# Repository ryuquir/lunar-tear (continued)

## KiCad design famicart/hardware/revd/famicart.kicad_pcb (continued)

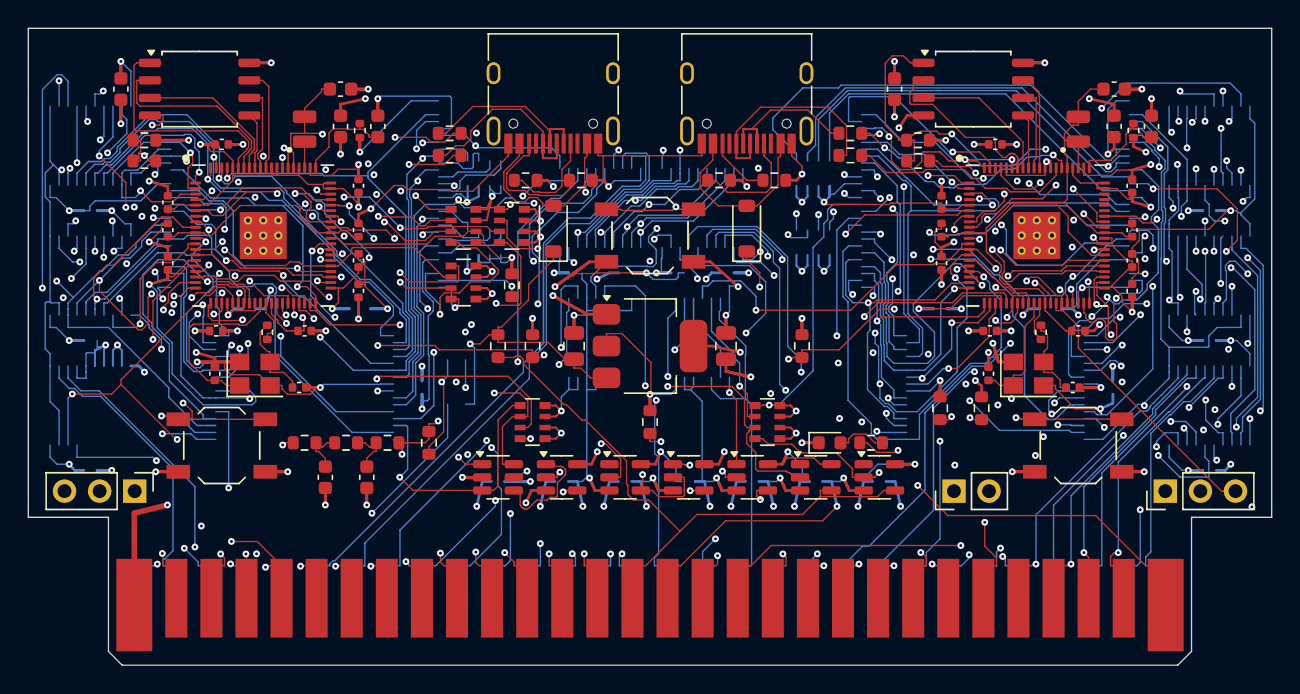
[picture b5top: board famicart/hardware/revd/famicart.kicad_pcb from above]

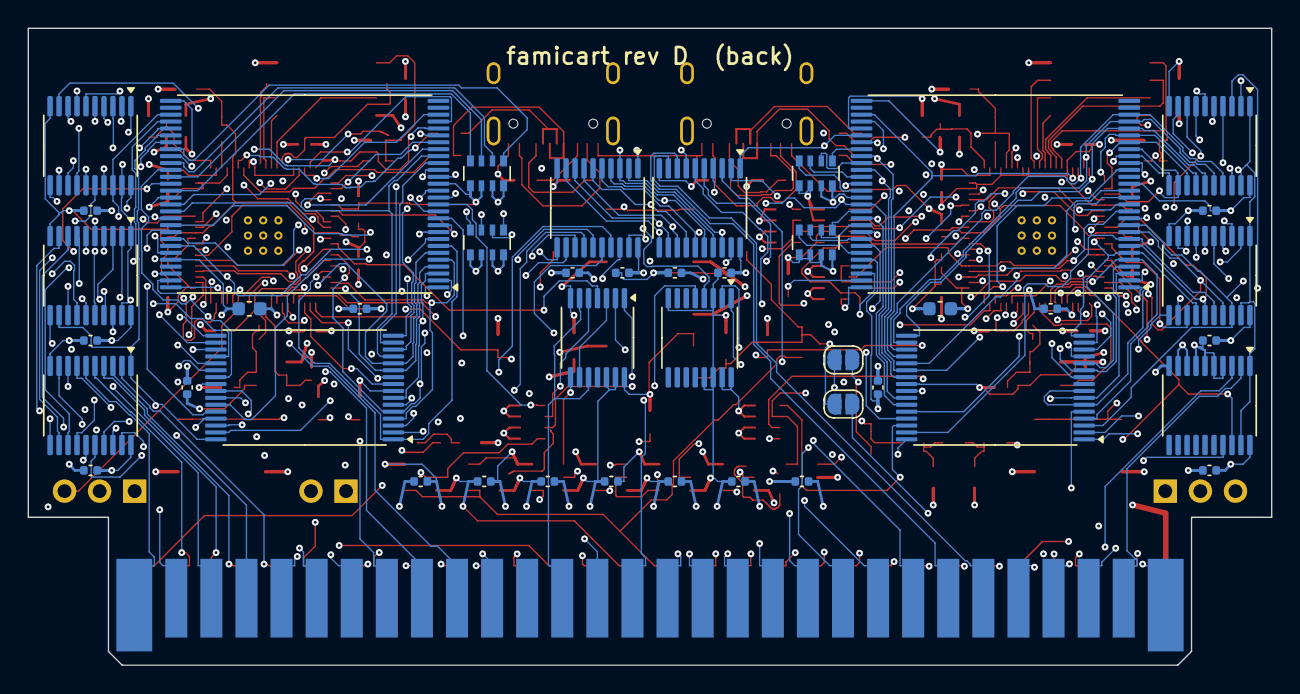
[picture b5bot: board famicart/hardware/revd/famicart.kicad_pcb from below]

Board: 6 copper layers, 90.0 x 46.1 mm, 140 parts (43 on the bottom side), 228 nets.

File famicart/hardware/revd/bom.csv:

Qty,Value,Footprint,References,Suggested part
1,Famicom 60-pin edge,Famicom_CardEdge_60,J1,"PCB card edge (gold fingers), no part"
2,RP2350B,QFN-80-1EP_10x10mm_P0.4mm_EP3.4x3.4mm,U1 U2,
2,W25Q16JVSSIQ,SOIC-8_5.23x5.23mm_P1.27mm,U3 U4,
2,100n,C_0603_1608Metric,C1 C17,X7R 0603 16V
9,10k,R_0603_1608Metric,R1 R7 R17 R22 R23 R24 R25 R26 R27,0603 1%
4,1k,R_0603_1608Metric,R2 R8 R21 R28,0603 1%
2,12MHz ABM8-272-T3,Crystal_SMD_3225-4Pin_3.2x2.5mm,Y1 Y2,
2,1k,R_0402_1005Metric,R3 R9,0603 1%
4,15p,C_0402_1005Metric,C2 C3 C18 C19,
2,3.3uH AOTA-B201610S3R3,L_0806_2016Metric,L1 L2,
6,4.7u,C_0603_1608Metric,C4 C5 C6 C20 C21 C22,
2,33,R_0402_1005Metric,R4 R10,
4,27,R_0603_1608Metric,R5 R6 R11 R12,
41,100n,C_0402_1005Metric,C7 C8 C9 C10 C11 C12 C13 C14 C15 C16 C23 C24 C25 C26 C27 C28 C29 C30 C31 C32 C37 C39 C41 C42 C43 C44 C45 C46 C47 C48 C49 C50 C51 C52 C53 C54 C55 C56 C57 C58 C59,X7R 0603 16V
1,USB-C PRG/mapper,USB_C_Receptacle_HRO_TYPE-C-31-M-12,J3,
4,5.1k,R_0603_1608Metric,R13 R14 R15 R16,0603 1% (USB-C CC pull-down)
1,USB-C CHR,USB_C_Receptacle_HRO_TYPE-C-31-M-12,J4,
2,B5819W,D_SOD-123,D1 D2,
1,RESET,SW_SPST_TL3342,SW1,E-Switch TL3342 / any 4.7x3.5 mm low-profile tactile
1,BOOTSEL A,SW_SPST_TL3342,SW2,
1,BOOTSEL B,SW_SPST_TL3342,SW3,
1,RUN/GND,PinHeader_1x02_P2.54mm_Vertical,J2,"2-pin 2.54 mm header (optional, wire to the console reset switch)"
1,SWD A,PinHeader_1x03_P2.54mm_Vertical,J5,
1,SWD B,PinHeader_1x03_P2.54mm_Vertical,J6,
1,AMS1117-3.3,SOT-223-3_TabPin2,U28,
2,10u,C_0805_2012Metric,C33 C34,X5R 0805 10V
2,2.2k,R_0603_1608Metric,R18 R19,0603 1%
1,4.7k,R_0603_1608Metric,R20,0603 1%
2,10n,C_0603_1608Metric,C35 C36,X7R 0603 50V
1,AUDIO bypass,SolderJumper-2_P1.3mm_Open_RoundedPad1.0x1.5mm,JP1,
1,CART_PRESENT,SolderJumper-2_P1.3mm_Open_RoundedPad1.0x1.5mm,JP2,
9,10k x4,R_Array_Convex_4x0603,RN1 RN2 RN3 RN4 RN5 RN6 RN7 RN8 RN9,
2,S29GL01GS 1Gbit NOR,TSOP-I-56_18.4x14mm_P0.5mm,U5 U6,
2,1u,C_0603_1608Metric,C38 C40,
1,FM28V100 128Kx8 F-RAM,TSOP-I-32_11.8x8mm_P0.5mm,U7,
1,IS62WV5128 512Kx8 SRAM,TSOP-I-32_11.8x8mm_P0.5mm,U8,
1,74LVC541 U9,TSSOP-20_4.4x6.5mm_P0.65mm,U9,
1,74LVC541 U10,TSSOP-20_4.4x6.5mm_P0.65mm,U10,
1,74LVC541 U11,TSSOP-20_4.4x6.5mm_P0.65mm,U11,
1,74LVC245 CPU data,TSSOP-20_4.4x6.5mm_P0.65mm,U12,
1,74LVC245 CPU->PPU data bridge,TSSOP-20_4.4x6.5mm_P0.65mm,U24,
1,74LVC139 CHR ROM/RAM select,TSSOP-16_4.4x5mm_P0.65mm,U22,
1,74LVC541 U17,TSSOP-20_4.4x6.5mm_P0.65mm,U17,
1,74LVC541 U18,TSSOP-20_4.4x6.5mm_P0.65mm,U18,
1,74LVC245 PPU data,TSSOP-20_4.4x6.5mm_P0.65mm,U19,
1,74LVC00 PPU access / CIRAM glue,TSSOP-14_4.4x5mm_P0.65mm,U20,
1,74LVC1G11 AND3: CPU data enable,SOT-23-6,U13,
1,74LVC1G32 OR: CPU 245 /OE,SOT-23-5,U14,
1,74LVC1G04 INV: R/W,SOT-23-5,U15,
1,74LVC1G00 NAND: WRAM /WE,SOT-23-5,U16,
1,74LVC1G32 OR: PPU 245 /OE,SOT-23-5,U21,
1,74LVC1G07 OD: /IRQ A,SOT-23-5,U26,
1,74LVC1G07 OD: /IRQ B,SOT-23-5,U27,
1,green 0603,LED_0603_1608Metric,D3,

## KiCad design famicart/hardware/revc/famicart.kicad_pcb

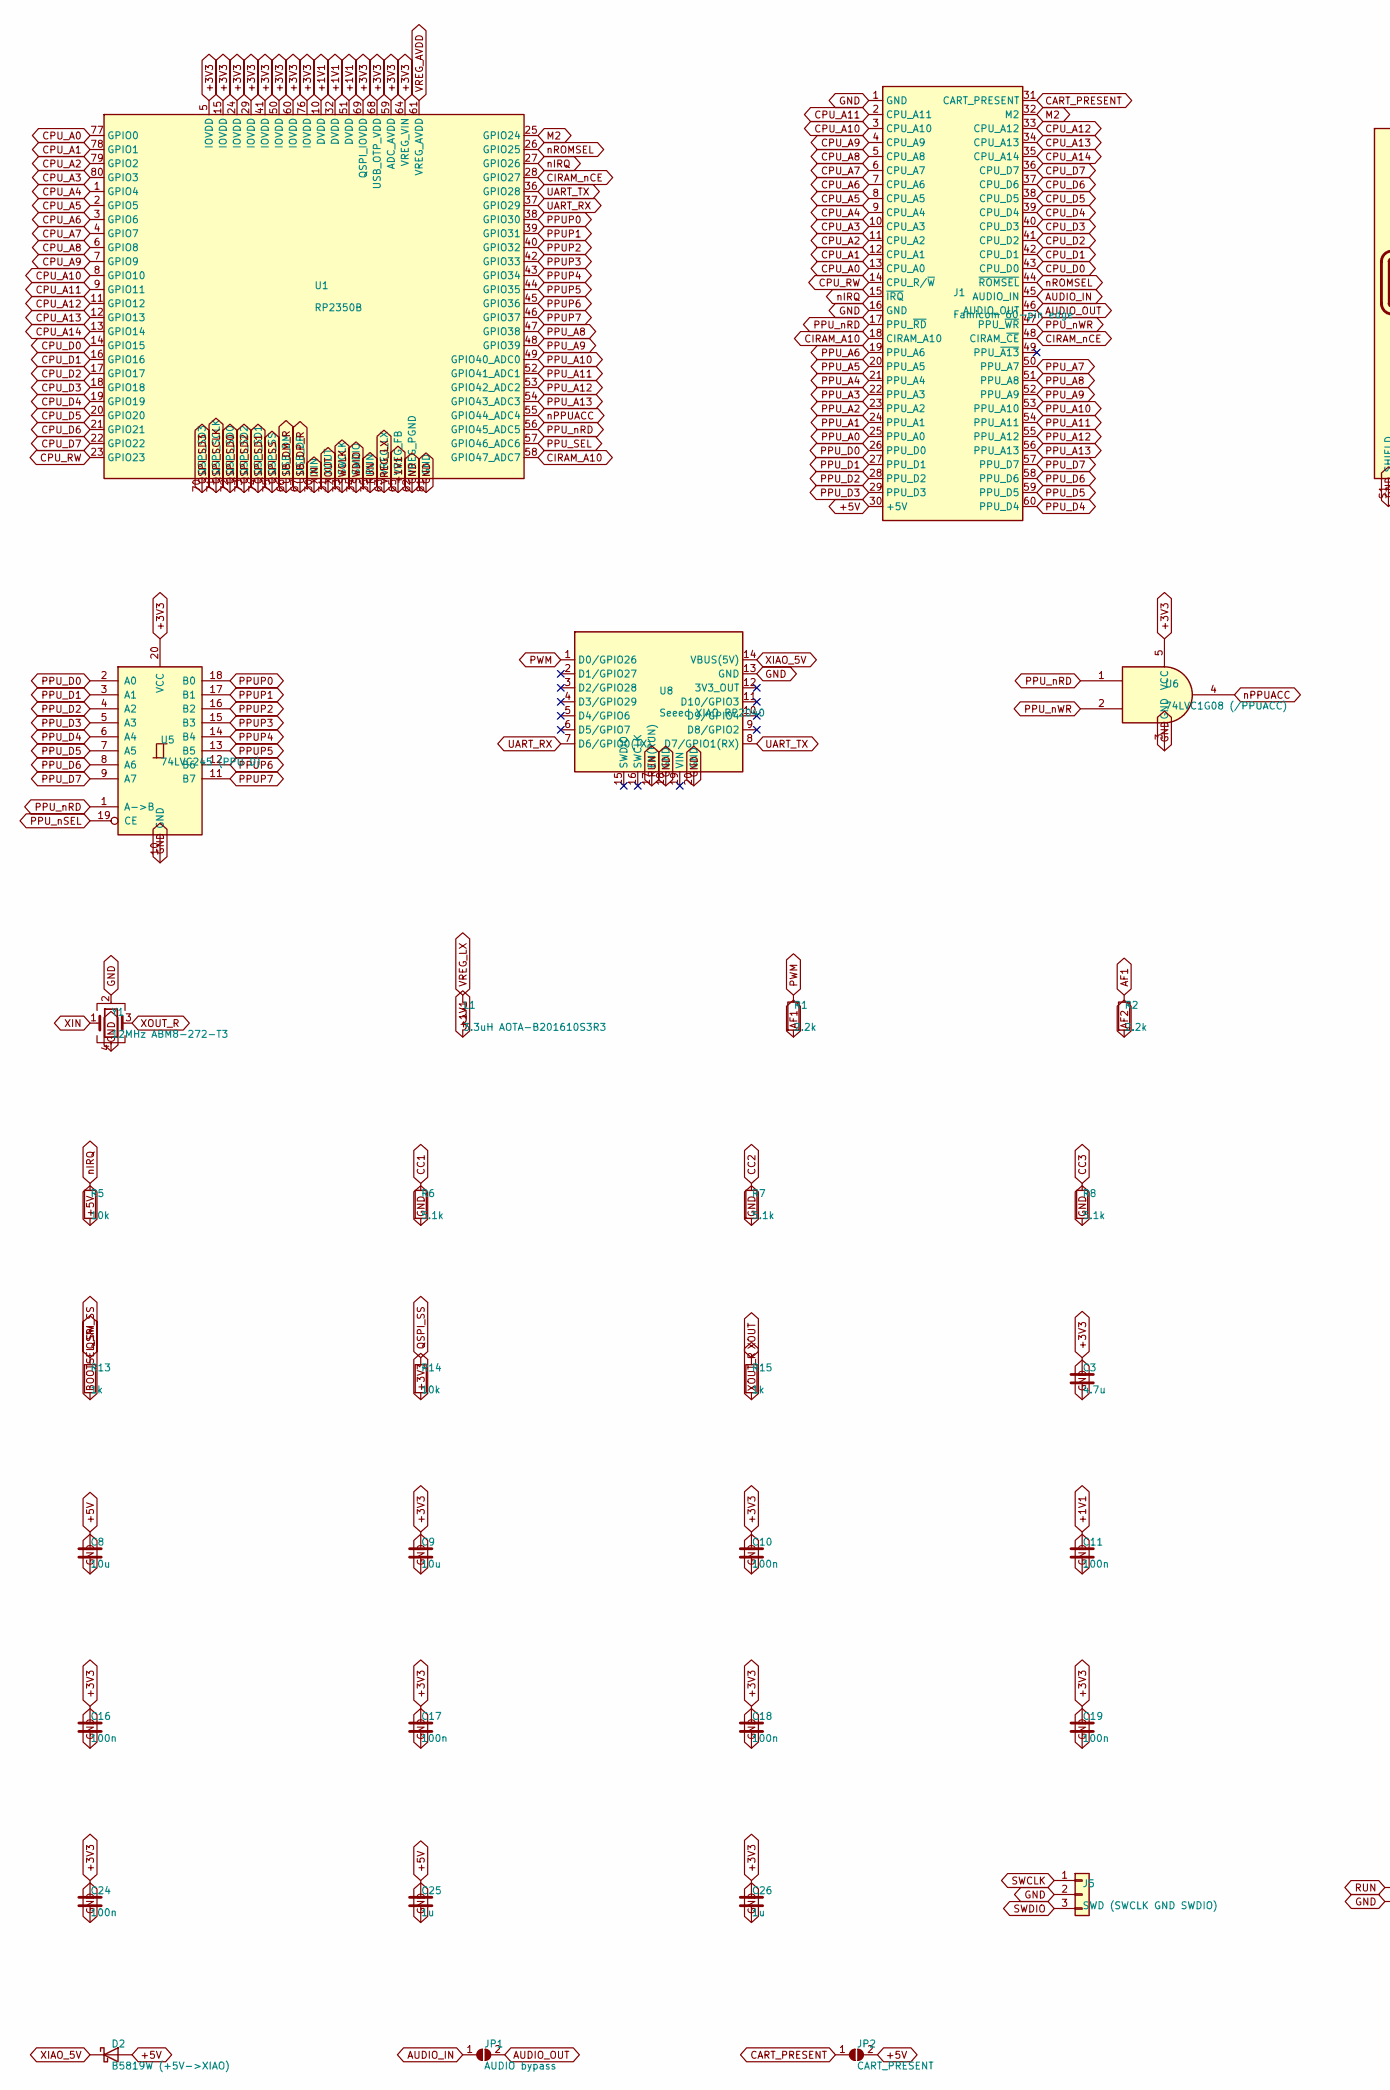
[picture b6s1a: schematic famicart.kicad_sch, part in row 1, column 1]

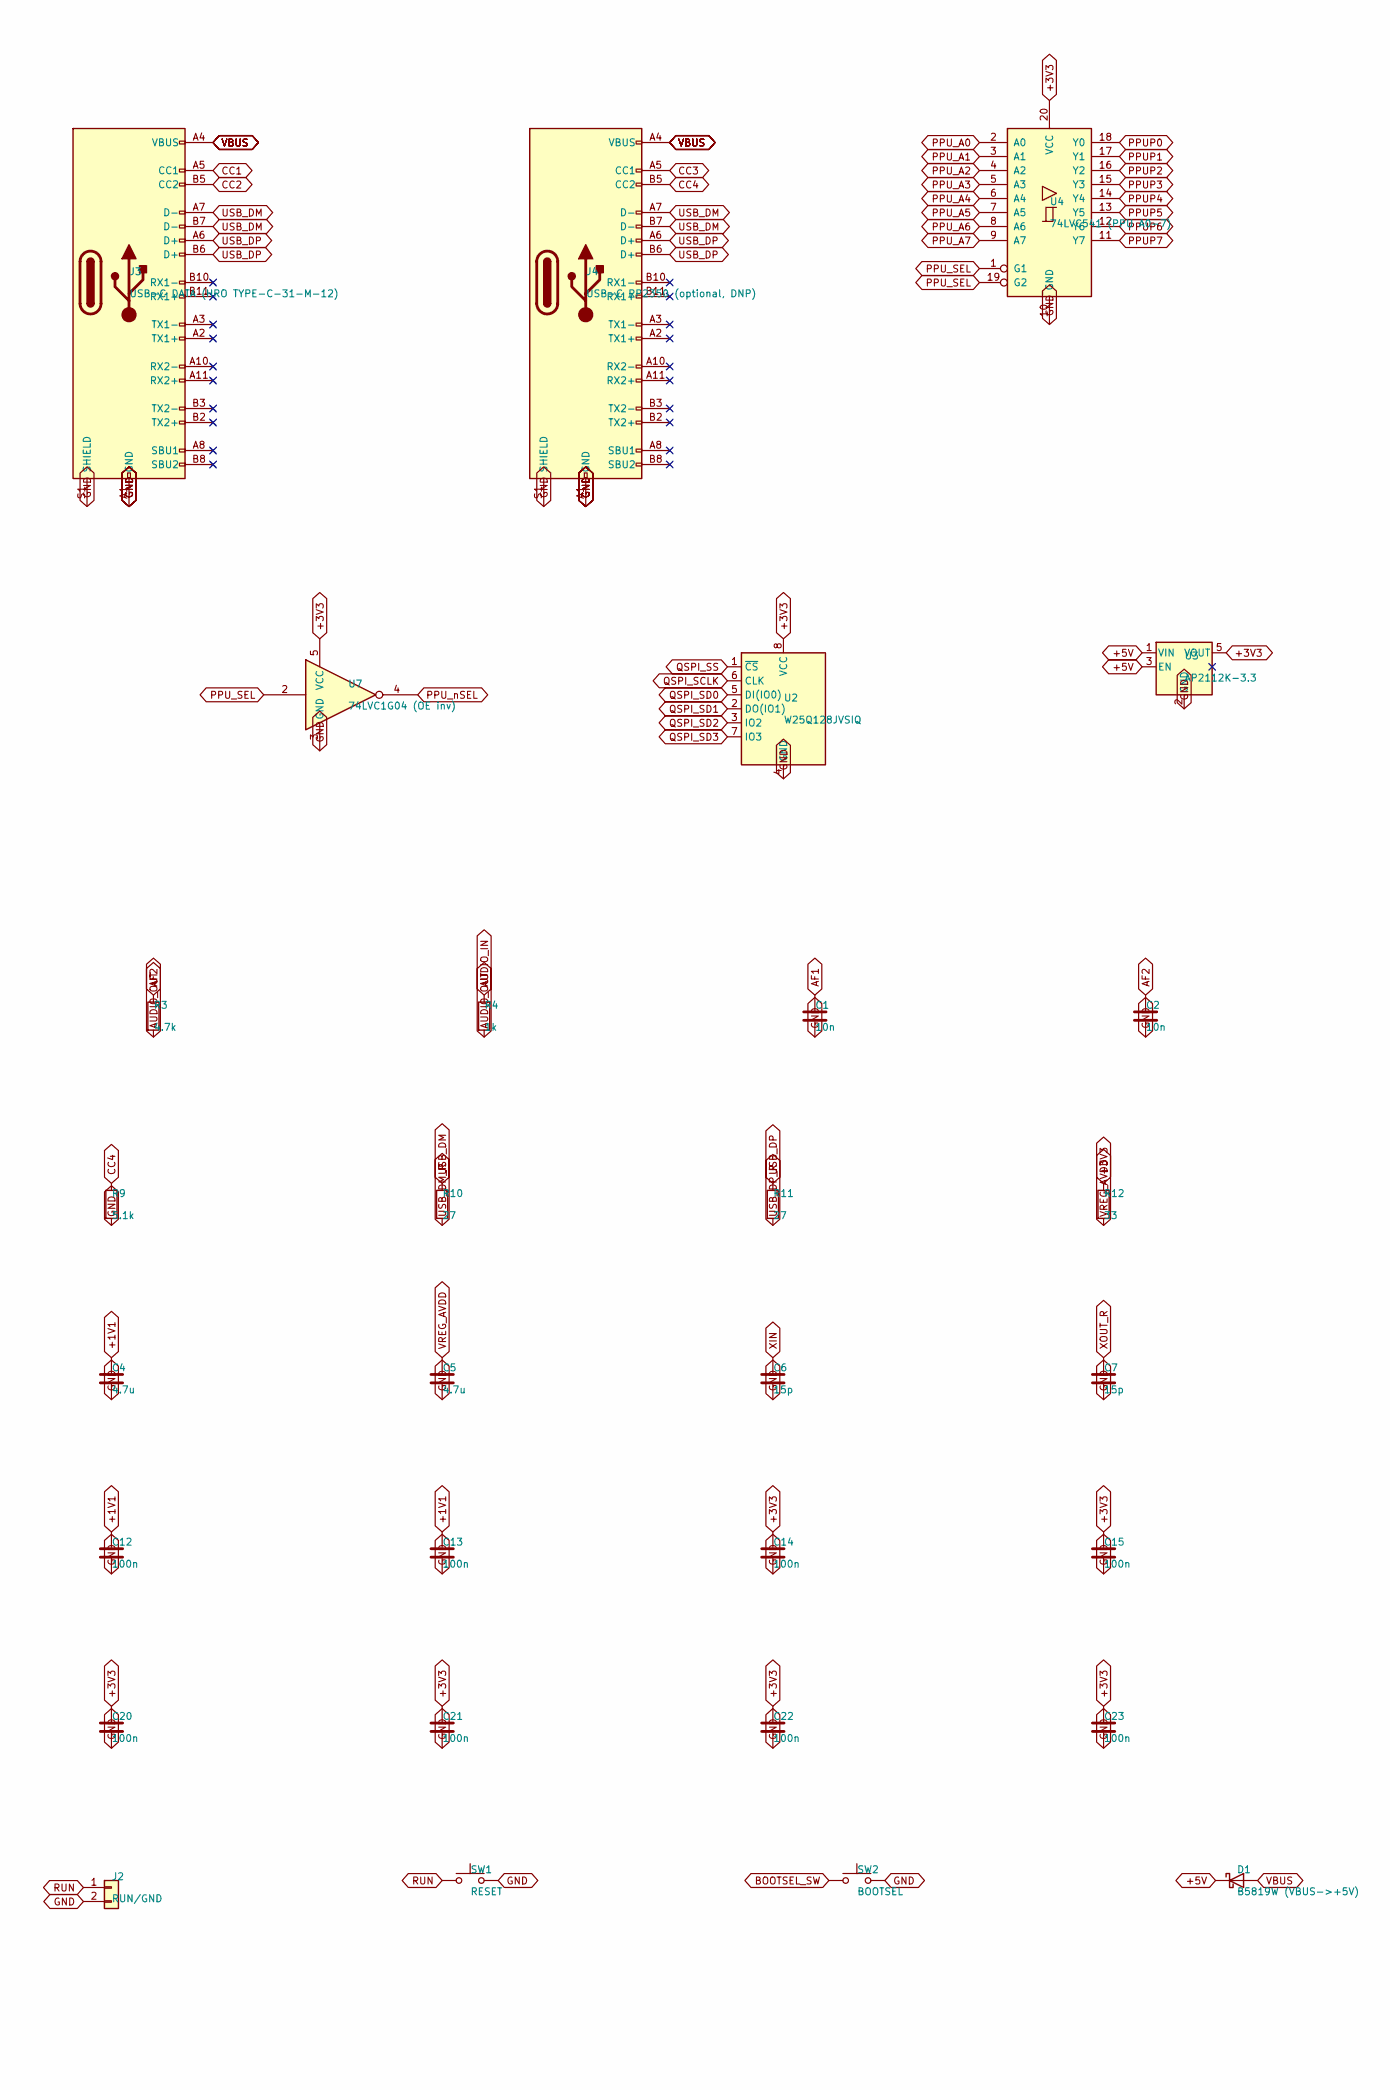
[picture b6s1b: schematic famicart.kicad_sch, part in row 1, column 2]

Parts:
C1, C2: 10n; C_0603_1608Metric
C3, C4, C5: 4.7u; C_0603_1608Metric
C6, C7: 15p; C_0402_1005Metric
C8, C9: 10u; C_0805_2012Metric
C10, C21, C22, C23, C24: 100n; C_0603_1608Metric
C11, C12, C13, C14, C15, C16, C17, C18, C19, C20: 100n; C_0402_1005Metric
C25, C26: 1u; C_0603_1608Metric
D1: B5819W (VBUS->+5V); D_SOD-123
D2: B5819W (+5V->XIAO); D_SOD-123
J1: Famicom 60-pin edge; Famicom_CardEdge_60
J2: RUN/GND; PinHeader_1x02_P2.54mm_Vertical
J3: USB-C DATA (HRO TYPE-C-31-M-12); USB_C_Receptacle_HRO_TYPE-C-31-M-12
J4: USB-C RP2350 (optional, DNP); USB_C_Receptacle_HRO_TYPE-C-31-M-12
J5: SWD (SWCLK GND SWDIO); PinHeader_1x03_P2.54mm_Vertical
JP1: AUDIO bypass; SolderJumper-2_P1.3mm_Open_RoundedPad1.0x1.5mm
JP2: CART_PRESENT; SolderJumper-2_P1.3mm_Open_RoundedPad1.0x1.5mm
L1: 3.3uH AOTA-B201610S3R3; L_0806_2016Metric
R1, R2: 2.2k; R_0603_1608Metric
R3: 4.7k; R_0603_1608Metric
R4, R13: 1k; R_0603_1608Metric
R5, R14: 10k; R_0603_1608Metric
R6, R7, R8, R9: 5.1k; R_0603_1608Metric
R10, R11: 27; R_0603_1608Metric
R12: 33; R_0402_1005Metric
R15: 1k; R_0402_1005Metric
SW1: RESET; SW_SPST_TL3342
SW2: BOOTSEL; SW_SPST_TL3342
U1: RP2350B; QFN-80-1EP_10x10mm_P0.4mm_EP3.4x3.4mm
U2: W25Q128JVSIQ; SOIC-8_5.23x5.23mm_P1.27mm
U3: AP2112K-3.3; SOT-23-5
U4: 74LVC541 (PPU A0-7); TSSOP-20_4.4x6.5mm_P0.65mm
U5: 74LVC245 (PPU D); TSSOP-20_4.4x6.5mm_P0.65mm
U6: 74LVC1G08 (/PPUACC); SOT-23-5
U7: 74LVC1G04 (OE inv); SOT-23-5
U8: Seeed XIAO RP2040; XIAO-RP2040-SMD
Y1: 12MHz ABM8-272-T3; Crystal_SMD_3225-4Pin_3.2x2.5mm

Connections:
+1V1: C4.1, C11.1, C12.1, C13.1, L1.2, U1.10 (DVDD), U1.32 (DVDD), U1.51 (DVDD), U1.65 (VREG_FB)
+3V3: C3.1, C9.1, C10.1, C14.1, C15.1, C16.1, C17.1, C18.1, C19.1, C20.1, C21.1, C22.1, C23.1, C24.1, C26.1, R12.1, R14.2, U1.5 (IOVDD), U1.15 (IOVDD), U1.24 (IOVDD), U1.29 (IOVDD), U1.41 (IOVDD), U1.50 (IOVDD), U1.59 (ADC_AVDD), U1.60 (IOVDD), U1.64 (VREG_VIN), U1.68 (USB_OTP_VDD), U1.69 (QSPI_IOVDD), U1.76 (IOVDD), U2.8 (VCC), U3.5 (VOUT), U4.20 (VCC), U5.20 (VCC), U6.5 (VCC), U7.5 (VCC)
+5V: C8.1, C25.1, D1.1 (K), D2.2 (A), J1.30 (+5V), JP2.2 (B), R5.2, U3.1 (VIN), U3.3 (EN)
AF1: C1.1, R1.2, R2.1
AF2: C2.1, R2.2, R3.1
AUDIO_IN: J1.45 (AUDIO_IN), JP1.1 (A), R4.1
AUDIO_OUT: J1.46 (AUDIO_OUT), JP1.2 (B), R3.2, R4.2
BOOTSEL_SW: R13.2, SW2.1
CART_PRESENT: J1.31 (CART_PRESENT), JP2.1 (A)
CC1: J3.A5 (CC1), R6.1
CC2: J3.B5 (CC2), R7.1
CC3: J4.A5 (CC1), R8.1
CC4: J4.B5 (CC2), R9.1
CIRAM_A10: J1.18 (CIRAM_A10), U1.58 (GPIO47_ADC7)
CIRAM_nCE: J1.48 (CIRAM_~CE), U1.28 (GPIO27)
CPU_A0: J1.13 (CPU_A0), U1.77 (GPIO0)
CPU_A1: J1.12 (CPU_A1), U1.78 (GPIO1)
CPU_A2: J1.11 (CPU_A2), U1.79 (GPIO2)
CPU_A3: J1.10 (CPU_A3), U1.80 (GPIO3)
CPU_A4: J1.9 (CPU_A4), U1.1 (GPIO4)
CPU_A5: J1.8 (CPU_A5), U1.2 (GPIO5)
CPU_A6: J1.7 (CPU_A6), U1.3 (GPIO6)
CPU_A7: J1.6 (CPU_A7), U1.4 (GPIO7)
CPU_A8: J1.5 (CPU_A8), U1.6 (GPIO8)
CPU_A9: J1.4 (CPU_A9), U1.7 (GPIO9)
CPU_A10: J1.3 (CPU_A10), U1.8 (GPIO10)
CPU_A11: J1.2 (CPU_A11), U1.9 (GPIO11)
CPU_A12: J1.33 (CPU_A12), U1.11 (GPIO12)
CPU_A13: J1.34 (CPU_A13), U1.12 (GPIO13)
CPU_A14: J1.35 (CPU_A14), U1.13 (GPIO14)
CPU_D0: J1.43 (CPU_D0), U1.14 (GPIO15)
CPU_D1: J1.42 (CPU_D1), U1.16 (GPIO16)
CPU_D2: J1.41 (CPU_D2), U1.17 (GPIO17)
CPU_D3: J1.40 (CPU_D3), U1.18 (GPIO18)
CPU_D4: J1.39 (CPU_D4), U1.19 (GPIO19)
CPU_D5: J1.38 (CPU_D5), U1.20 (GPIO20)
CPU_D6: J1.37 (CPU_D6), U1.21 (GPIO21)
CPU_D7: J1.36 (CPU_D7), U1.22 (GPIO22)
CPU_RW: J1.14 (CPU_R/~W), U1.23 (GPIO23)
GND: C1.2, C2.2, C3.2, C4.2, C5.2, C6.2, C7.2, C8.2, C9.2, C10.2, C11.2, C12.2, C13.2, C14.2, C15.2, C16.2, C17.2, C18.2, C19.2, C20.2, C21.2, C22.2, C23.2, C24.2, C25.2, C26.2, J1.1 (GND), J1.16 (GND), J2.2, J3.A1 (GND), J3.A12 (GND), J3.B1 (GND), J3.B12 (GND), J3.S1 (SHIELD), J4.A1 (GND), J4.A12 (GND), J4.B1 (GND), J4.B12 (GND), J4.S1 (SHIELD), J5.2, R6.2, R7.2, R8.2, R9.2, SW1.2, SW2.2, U1.62 (VREG_PGND), U1.81 (GND), U2.4 (GND), U3.2 (GND), U4.10 (GND), U5.10 (GND), U6.3 (GND), U7.3 (GND), U8.13 (GND), U8.18 (GND), U8.20 (GND), Y1.2, Y1.4
M2: J1.32 (M2), U1.25 (GPIO24)
PPUP0: U1.38 (GPIO30), U4.18 (Y0), U5.18 (B0)
PPUP1: U1.39 (GPIO31), U4.17 (Y1), U5.17 (B1)
PPUP2: U1.40 (GPIO32), U4.16 (Y2), U5.16 (B2)
PPUP3: U1.42 (GPIO33), U4.15 (Y3), U5.15 (B3)
PPUP4: U1.43 (GPIO34), U4.14 (Y4), U5.14 (B4)
PPUP5: U1.44 (GPIO35), U4.13 (Y5), U5.13 (B5)
PPUP6: U1.45 (GPIO36), U4.12 (Y6), U5.12 (B6)
PPUP7: U1.46 (GPIO37), U4.11 (Y7), U5.11 (B7)
PPU_A0: J1.25 (PPU_A0), U4.2 (A0)
PPU_A1: J1.24 (PPU_A1), U4.3 (A1)
PPU_A2: J1.23 (PPU_A2), U4.4 (A2)
PPU_A3: J1.22 (PPU_A3), U4.5 (A3)
PPU_A4: J1.21 (PPU_A4), U4.6 (A4)
PPU_A5: J1.20 (PPU_A5), U4.7 (A5)
PPU_A6: J1.19 (PPU_A6), U4.8 (A6)
PPU_A7: J1.50 (PPU_A7), U4.9 (A7)
PPU_A8: J1.51 (PPU_A8), U1.47 (GPIO38)
PPU_A9: J1.52 (PPU_A9), U1.48 (GPIO39)
PPU_A10: J1.53 (PPU_A10), U1.49 (GPIO40_ADC0)
PPU_A11: J1.54 (PPU_A11), U1.52 (GPIO41_ADC1)
PPU_A12: J1.55 (PPU_A12), U1.53 (GPIO42_ADC2)
PPU_A13: J1.56 (PPU_A13), U1.54 (GPIO43_ADC3)
PPU_D0: J1.26 (PPU_D0), U5.2 (A0)
PPU_D1: J1.27 (PPU_D1), U5.3 (A1)
PPU_D2: J1.28 (PPU_D2), U5.4 (A2)
PPU_D3: J1.29 (PPU_D3), U5.5 (A3)
PPU_D4: J1.60 (PPU_D4), U5.6 (A4)
PPU_D5: J1.59 (PPU_D5), U5.7 (A5)
PPU_D6: J1.58 (PPU_D6), U5.8 (A6)
PPU_D7: J1.57 (PPU_D7), U5.9 (A7)
PPU_SEL: U1.57 (GPIO46_ADC6), U4.1 (G1), U4.19 (G2), U7.2
PPU_nRD: J1.17 (PPU_~RD), U1.56 (GPIO45_ADC5), U5.1 (A->B), U6.1
PPU_nSEL: U5.19 (CE), U7.4
PPU_nWR: J1.47 (PPU_~WR), U6.2
PWM: R1.1, U8.1 (D0/GPIO26)
QSPI_SCLK: U1.71 (QSPI_SCLK), U2.6 (CLK)
QSPI_SD0: U1.72 (QSPI_SD0), U2.5 (DI(IO0))
QSPI_SD1: U1.74 (QSPI_SD1), U2.2 (DO(IO1))
QSPI_SD2: U1.73 (QSPI_SD2), U2.3 (IO2)
QSPI_SD3: U1.70 (QSPI_SD3), U2.7 (IO3)
QSPI_SS: R13.1, R14.1, U1.75 (QSPI_SS), U2.1 (~CS)
RUN: J2.1, SW1.1, U1.35 (RUN), U8.17 (EN(RUN))
SWCLK: J5.1, U1.33 (SWCLK)
SWDIO: J5.3, U1.34 (SWDIO)
UART_RX: U1.37 (GPIO29), U8.7 (D6/GPIO0(TX))
UART_TX: U1.36 (GPIO28), U8.8 (D7/GPIO1(RX))
USB_DM: J3.A7 (D-), J3.B7 (D-), J4.A7 (D-), J4.B7 (D-), R10.1
USB_DM_R: R10.2, U1.66 (USB_DM)
USB_DP: J3.A6 (D+), J3.B6 (D+), J4.A6 (D+), J4.B6 (D+), R11.1
USB_DP_R: R11.2, U1.67 (USB_DP)
VBUS: D1.2 (A), J3.A4 (VBUS), J3.A9 (VBUS), J3.B4 (VBUS), J3.B9 (VBUS), J4.A4 (VBUS), J4.A9 (VBUS), J4.B4 (VBUS), J4.B9 (VBUS)
VREG_AVDD: C5.1, R12.2, U1.61 (VREG_AVDD)
VREG_LX: L1.1, U1.63 (VREG_LX)
XIAO_5V: D2.1 (K), U8.14 (VBUS(5V))
XIN: C6.1, U1.30 (XIN), Y1.1
XOUT: R15.1, U1.31 (XOUT)
XOUT_R: C7.1, R15.2, Y1.3
nIRQ: J1.15 (~IRQ), R5.1, U1.27 (GPIO26)
nPPUACC: U1.55 (GPIO44_ADC4), U6.4
nROMSEL: J1.44 (~ROMSEL), U1.26 (GPIO25)

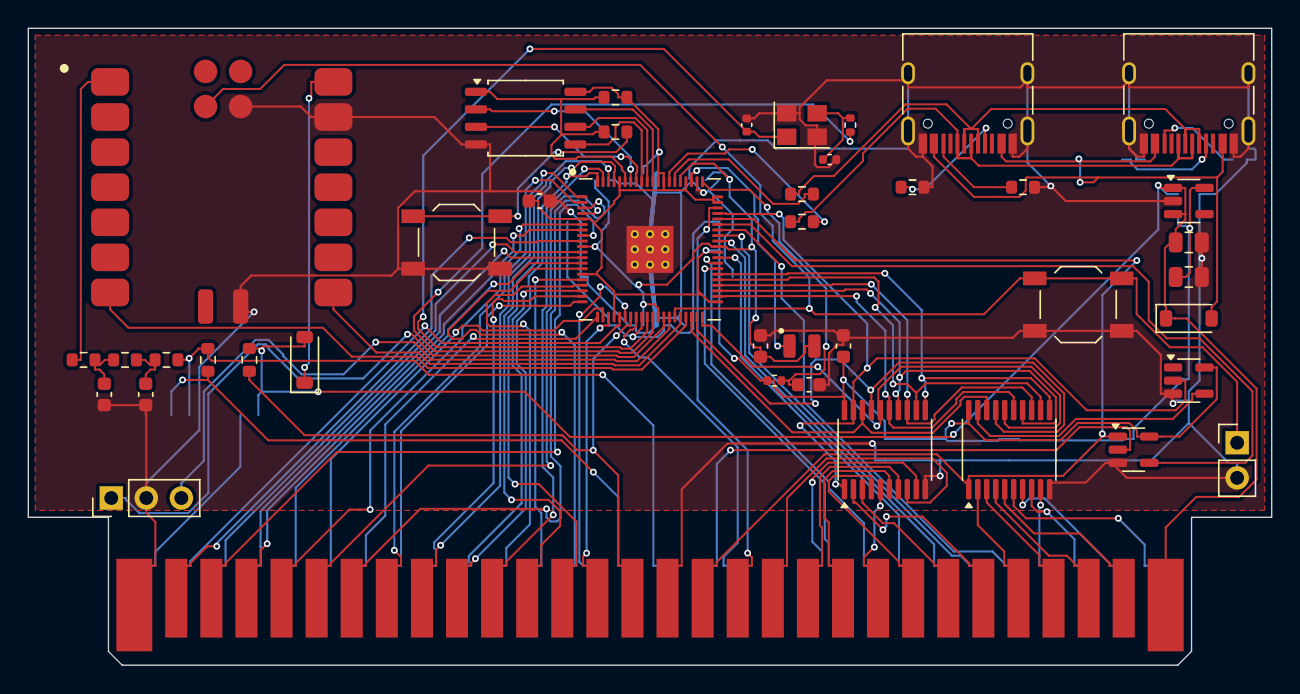
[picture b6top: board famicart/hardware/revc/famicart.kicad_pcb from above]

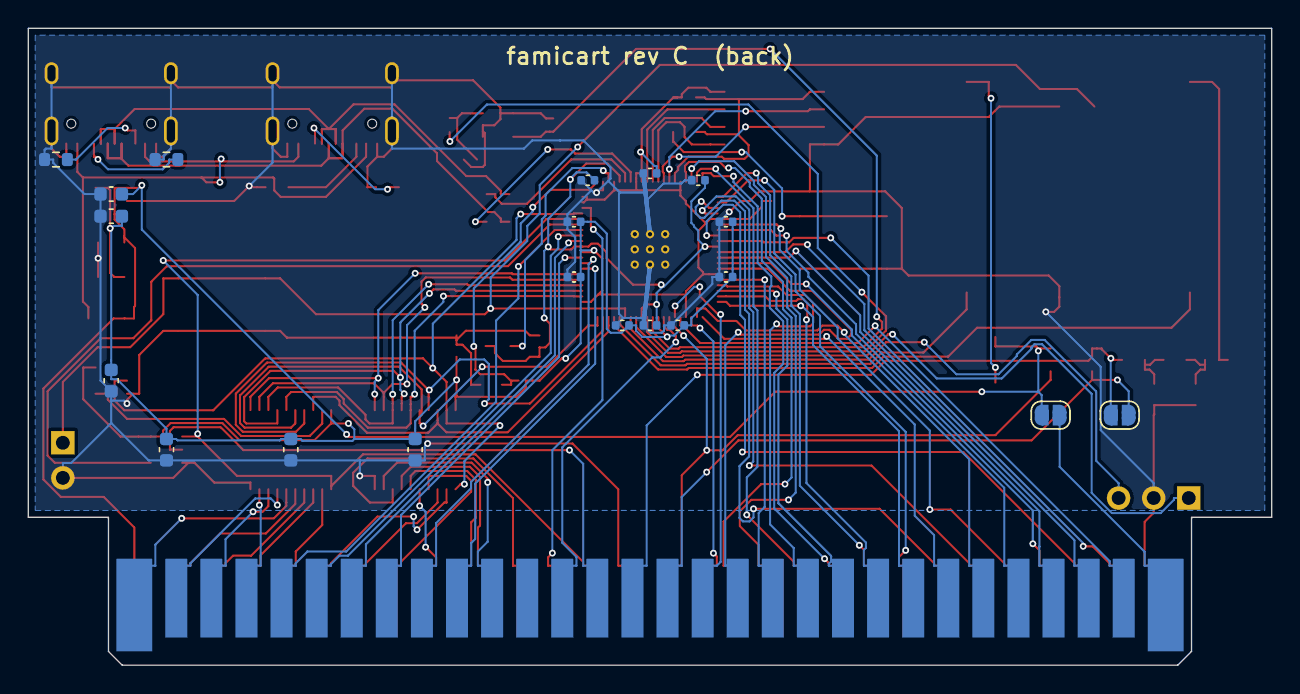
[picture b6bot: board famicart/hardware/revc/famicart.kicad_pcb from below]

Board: 2 copper layers, 90.0 x 46.1 mm, 62 parts (20 on the bottom side), 101 nets.

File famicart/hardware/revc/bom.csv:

Qty,Value,Footprint,References,Suggested part
1,Famicom 60-pin edge,Famicom_CardEdge_60,J1,"PCB card edge (gold fingers), no part"
1,RP2350B,QFN-80-1EP_10x10mm_P0.4mm_EP3.4x3.4mm,U1,
1,W25Q128JVSIQ,SOIC-8_5.23x5.23mm_P1.27mm,U2,
1,AP2112K-3.3,SOT-23-5,U3,
1,74LVC541,TSSOP-20_4.4x6.5mm_P0.65mm,U4,Nexperia 74LVC541APW (TSSOP-20)
1,74LVC245,TSSOP-20_4.4x6.5mm_P0.65mm,U5,Nexperia 74LVC245APW (TSSOP-20)
1,74LVC1G08,SOT-23-5,U6,Nexperia 74LVC1G08GW / TI SN74LVC1G08DBV
1,74LVC1G04,SOT-23-5,U7,
1,Seeed XIAO RP2040,XIAO-RP2040-SMD,U8,
1,12MHz ABM8-272-T3,Crystal_SMD_3225-4Pin_3.2x2.5mm,Y1,
1,3.3uH AOTA-B201610S3R3,L_0806_2016Metric,L1,
1,USB-C DATA,USB_C_Receptacle_HRO_TYPE-C-31-M-12,J3,
1,USB-C RP2350,USB_C_Receptacle_HRO_TYPE-C-31-M-12,J4,
1,RUN/GND,PinHeader_1x02_P2.54mm_Vertical,J2,"2-pin 2.54 mm header (optional, wire to the console reset switch)"
1,SWD,PinHeader_1x03_P2.54mm_Vertical,J5,
1,RESET,SW_SPST_TL3342,SW1,E-Switch TL3342 / any 4.7x3.5 mm low-profile tactile
1,BOOTSEL,SW_SPST_TL3342,SW2,
2,2.2k,R_0603_1608Metric,R1 R2,0603 1%
1,4.7k,R_0603_1608Metric,R3,0603 1%
2,1k,R_0603_1608Metric,R4 R13,0603 1%
2,10n,C_0603_1608Metric,C1 C2,X7R 0603 50V
2,10k,R_0603_1608Metric,R5 R14,0603 1%
4,5.1k,R_0603_1608Metric,R6 R7 R8 R9,0603 1% (USB-C CC pull-down)
2,27,R_0603_1608Metric,R10 R11,
1,33,R_0402_1005Metric,R12,
1,1k,R_0402_1005Metric,R15,0603 1%
3,4.7u,C_0603_1608Metric,C3 C4 C5,
2,15p,C_0402_1005Metric,C6 C7,
2,10u,C_0805_2012Metric,C8 C9,X5R 0805 10V
5,100n,C_0603_1608Metric,C10 C21 C22 C23 C24,X7R 0603 16V
2,B5819W,D_SOD-123,D1 D2,
1,AUDIO bypass,SolderJumper-2_P1.3mm_Open_RoundedPad1.0x1.5mm,JP1,
1,CART_PRESENT,SolderJumper-2_P1.3mm_Open_RoundedPad1.0x1.5mm,JP2,
10,100n,C_0402_1005Metric,C11 C12 C13 C14 C15 C16 C17 C18 C19 C20,X7R 0603 16V
2,1u,C_0603_1608Metric,C25 C26,

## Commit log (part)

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2026-03-16 [major, quest flow fix]
2026-03-17 Refactor Gacha and Scene Management in README and Code
    - Updated README to reflect changes in bootstrap options, replacing `--bootstrap-profile` with `--scene` for user initialization.
    - Refactored main.go to accommodate the new scene-based bootstrapping, enhancing user state management.
    - Adjusted Gacha catalog loading and related functions to ensure consistency with updated identifiers and improve clarity in asset resolution.
    - Removed obsolete functions and variables related to Gacha and quest handling, streamlining the codebase for better maintainability.
2026-03-18 Remove mock package and enhance quest flow engine with new scene and costume management
    - Deleted the mock package as it was no longer needed.
    - Introduced new types for scene grants and costumes in the quest flow engine to improve data handling.
    - Updated the engine to apply scene grants during quest progress, enhancing user experience.
    - Modified user state to include weapon notes and ensure comprehensive updates across user interactions.
2026-03-19 Update .gitignore and remove empty .keep file in frida directory
    - Added 'frida/' to .gitignore to exclude the frida directory from version control.
    - Deleted the empty .keep file in the frida directory to clean up the project structure.
2026-03-19 Refactor Quest Handling and Improve Logging
    - Updated ApplyBootstrap method to replace panic with a fatal log for unknown scene IDs, enhancing error handling.
    - Modified HandleQuestFinish method to include an isRetired parameter, improving quest completion logic.
    - Added new user data types (IUserConsumableItem, IUserMaterial, IUserImportantItem) to various service components for better state management.
    - Cleaned up state projection by removing unused user data types, streamlining data representation.
2026-03-20 Add Tutorial Unlock Conditions and Update User State Management
    - Introduced tutorialUnlockCondition struct to manage tutorial unlock criteria, enhancing tutorial progression logic.
    - Updated Engine to load tutorial unlock conditions from JSON, improving initialization of tutorial states.
    - Refactored UserState to use a map for storing multiple tutorial progress states, allowing for better management of user tutorials.
    - Enhanced state projection to sort and represent tutorial progress accurately, ensuring comprehensive user data handling.
2026-03-22 Enhance Quest Flow with Battle Drop Rewards
    - Updated the quest engine to include battle drop rewards, allowing for dynamic reward allocation based on quest completion.
    - Modified the StartMainQuest and FinishMainQuest methods to return battle drop rewards in the response, improving user feedback during quest progression.
    - Introduced new data structures for managing battle drop rewards and pickup reward groups, enhancing the overall quest reward system.
2026-03-22 Refactor Server into Domain-Oriented Architecture
    - Extract repository interfaces (UserRepository, SessionRepository,
    GachaRepository) from monolithic store.go; move MemoryStore to
    store/memory/ sub-package with error returns for DB compatibility
    - Split questflow/engine.go (1451 lines) into engine, rewards, battle,
    bootstrap, scene files
    - Replace monolithic state_projection.go with table-driven projector
2026-03-24 Enhance Main Quest Scene Progress Handling
    - Added logic to determine if the user has reached the last quest scene, updating MainQuest.IsReachedLastQuestScene accordingly.
    - Updated user portal cage status to reflect current progress and latest version during scene progress handling.
    - Adjusted user data diff to include IUserPortalCageStatus and IUserQuest, improving state management during quest updates.
2026-03-25 Add Snapshot Management for User State
    - Introduced snapshot functionality to save and load user state based on the current quest scene.
    - Updated MemoryStore to handle snapshot directory and scene ID during user state updates.
    - Enhanced user state initialization to load from snapshots if available, improving user experience during quest progression.
    - Added new methods for saving and loading snapshots in memory store, ensuring persistent user state across sessions.
    - Updated .gitignore to exclude snapshot files from version control.
2026-03-25 Implement Character Viewer Feature
    - Added CharacterViewer service to manage character viewing functionality.
    - Introduced CharacterViewerCatalog to handle character viewer fields and their release conditions.
    - Updated gRPC server to register the new CharacterViewer service and its dependencies.
    - Modified Makefile to include the new proto file for character viewer.
    - Enhanced main application entry point to initialize the character viewer catalog.
    - Implemented logic for retrieving released character viewer fields based on user quest state.
2026-03-28 Update CHANGELOG with new features and enhancements for 2026-03-28
2026-03-29 Add Fast Purchase Methods to IAP Patching
    - Updated `patch_apk.py` to include new methods for fast purchasing, allowing users to skip certain checks during in-app purchases.
    - Added patches to bypass the `CheckPurchasingAlert` and `_initialized` checks, improving the efficiency of the purchasing process.
    - Modified the patching output message to reflect the inclusion of fast purchase functionality.
2026-04-02 Add Weapon Management Features
    - Introduced WeaponService to handle weapon enhancements, including material consumption and experience tracking.
    - Added support for weapon skills and abilities in user state, allowing for detailed weapon management.
    - Implemented loading and cataloging of weapon data, including enhancements and experience thresholds.
    - Updated gRPC server to register the new WeaponService and its associated methods.
    - Enhanced user data projections to include weapon skills and abilities, improving client-side data handling.
2026-04-02 Add shared ConditionResolver and GimmickCatalog for server-side gimmick data
    Extract evaluate-condition logic into a reusable ConditionResolver, refactor
    CharacterViewerCatalog to use it, and add GimmickCatalog that populates
    IUserGimmickSequence entries in InitSequenceSchedule based on active schedules.
2026-04-03 Add Mythic Slab Features
    - Introduced CharacterBoardCatalog and CharacterBoardService to manage character board data, including panel releases and status effects.
    - Implemented loading and handling of character board data from JSON files, enhancing user experience with character board interactions.
    - Updated user state to include character board abilities and status ups, improving tracking of user progress and character enhancements.
    - Registered new user data projections for character boards, ensuring accurate client-side representation of character board states.
    - Modified gRPC server to register the new CharacterBoardService and its associated methods, integrating it into the existing ser
2026-04-04 Add Memoir Reward Features
    - Introduced PartsRow structure to manage parts data, including IDs and lottery group associations.
    - Updated QuestCatalog to load and index parts data, enhancing quest-related functionalities.
    - Enhanced user state to include PartsGroupNotes for tracking parts acquisition and status.
    - Implemented logic in QuestHandler to manage parts rewards and user state updates, improving user experience.
    - Registered new user data projections for parts and parts group notes, ensuring accurate client-side representation.
2026-04-04 Add Costume Awakening Features
    - Introduced new data structures for costume awakening, including CostumeAwakenRow, CostumeAwakenEffectRow, and related types to manage awakening effects and item acquisition.
    - Enhanced CostumeCatalog to support awakening data, allowing for dynamic loading and management of awakening-related information.
    - Implemented awakening logic in CostumeService, enabling users to awaken costumes with associated effects and status updates.
    - Updated user state to track costume awakening status, ensuring accurate representation of user progress and effects.
    - Enhanced data projection for costume awakening status, improving client-side synchronization and representation of
2026-04-04 Add Shop Catalog Enhancements
    - Introduced new data structures for shop management, including shopRow, shopItemCellGroupRow, and shopItemCellRow to facilitate item organization.
    - Implemented loading of shop data from JSON files, enhancing the ShopCatalog with an ItemShopPool for dynamic item management.
    - Updated user state handling in ShopServiceServer to incorporate the new item shop pool, improving user experience with replaceable shop items.
    - Enhanced sorting logic for item display in the shop, ensuring items are presented in a user-friendly order.
2026-04-05 Add Sell RPCs for Material, Parts, and Weapon services with DeleteTracker
    Implement MaterialService/Sell, PartsService/Sell, and WeaponService/Sell
    RPCs. Introduce DeleteTracker to properly send DeleteKeysJson when items
    are removed from user state, and apply it to existing Rebirth and
    ReleasePanel handlers as well.
2026-04-06 Enhance Weapon Story Unlock Logic in QuestHandler
    - Updated grantWeapon method to handle multiple weapon story release conditions, including acquisition and quest clear types.
    - Implemented logic to grant weapon story unlocks based on quest completion state, improving user experience with weapon rewards.
2026-04-06 Enhance Weapon Skill and Ability Management in WeaponService
    - Introduced new data structures for weapon skill and ability enhancement, including WeaponSkillEnhanceMaterialRow and WeaponAbilityEnhanceMaterialRow, to support skill and ability upgrades.
    - Updated WeaponCatalog to include mappings for skill and ability enhancement materials, improving organization and access to related data.
    - Implemented EnhanceSkill and EnhanceAbility methods in WeaponServiceServer to handle skill and ability enhancement logic, including material cost deduction and level management.
    - Enhanced logging for skill and ability enhancement processes to improve traceability and user experience.
2026-04-07 Add MainQuestRouteRow Structure and Enhance Quest Handling Logic
    - Introduced MainQuestRouteRow structure to manage quest route data, including MainQuestRouteId, MainQuestSeasonId, SortOrder, and CharacterId.
    - Updated LoadQuestCatalog function to read and process main quest route data, mapping season IDs by route IDs for improved quest management.
    - Enhanced HandleQuestStart method to set MainQuestSeasonId based on the route ID, improving user state management during quest flow.
    - Added SetRoute method in QuestServiceServer to update user quest route and season ID, ensuring accurate tracking of user progress.
2026-04-09 Implement Deck Skins Support
2026-04-10 Enhance Gacha Pool Logic and Exclude Evolved Weapons
    - Added functionality to load weapon evolution group data and build a set of evolved weapons to be excluded from the gacha pool.
    - Refactored gacha pool item selection logic to skip evolved weapons, improving the integrity of the gacha draw process.
    - Updated logging to provide insights on the number of excluded evolved weapons, enhancing traceability in gacha operations.
    - Utilized the 'slices' package for sorting weapon IDs, streamlining the sorting process in the gacha pool logic.
2026-04-10 Implement Big Hunt service
    Add BigHuntService with all RPCs (start, finish, restart, skip, save
    battle info, get top data), reward service, master data catalog, user
    state, and client projections. Create dedicated Big Hunt quest handlers
    to avoid corrupting main quest state.
2026-04-13 Update README with legal disclaimer and asset usage warnings
